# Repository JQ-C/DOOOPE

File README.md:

# DOOOPE. Real or Fake?

DOOOPE Keyboard is a 34-key wireless split keyboard. That uses Redragon low profile switches.

## Design Philosophy
DOOOPE was created with these in mind
- Budget at each category (MCU, Switch, Keycaps)
- Modular & Reusable parts
- Low Cost
- Low Profile
- Wireless
- 34 keys

# Resources

[Here](Kicad) you can find the Kicad files. 
<br>
[ZMK Config](https://github.com/JQ-C/zmk-config) for the DOOOPE using Xiao BLe

# Bill of Material
The link provided will be actual store i bought from but not affiliated with.
|Component|Amount|Remarks|Link|
|:----|:----|:----|:----|
|DOOOPE PCB|2|-| |
|SEEED Xiao BLE|2|-|[Cytron](https://my.cytron.io/p-seeed-xiao-ble-nrf52840-bluetooth-5p0)|
|Rechargeable Battery|2|28 x 18mm max| |
|Reset Switch|2|Through hole| |
|Power Switch|2|MSK12C02| [Shopee](https://shopee.com.my/10PCS-Slide-Switch-Micro-power-Toggle-Switch-Single-and-Double-row-Direct-inserted-Horizontal-Sliding-Second-Gear-Third-Gear-i.313127058.3661530160)|
|Pogo Pins|4|5mm|[Aliexpress](https://www.aliexpress.com/item/1005004016701633.html)|
|Redragon Switches|34|5mm|[Shopee](https://shopee.com.my/Redragon-SMD-RGB-MX-Low-Profile-Switch-3-Pin-for-Keyboard-Red-Black-Blue-Brown-i.326526863.10495732994?)|
|2mm male socket pins|4|1x7| |
|2.54 machine header pins|4|1x7| |
|JST PH 2.0 Connetor|2 Pair |-|[Shopee](https://shopee.com.my/10Sets-Lot-PH2.0-PH-2mm-Connector-Straight-needle-Seat-Plug-Terminals-2P-3P-4P-5P-6P-7P-8P-9P-10P-Connector-Pitch-2.0-i.313127058.5356644366?xptdk=3eb6c85b-3d97-453c-a1a4-ad3d53b7b325)|

# Build Guide
Coming soon <br>
The build guide for the DOOOPE keyboard can be found [here]()

# Project Reason
- DOOOPE keyboard was created to use Redragon low profile switch as a cheap alternative to the Low profile choc switches used in many Low-pro boards, hence the name "DOOOPE" that sounds like dupe.
- Another decision is to use off the shelf components and the cheapest at each category.
- This keyboard also used [Ergogen V4]() to prototype the layout and later finished in Kicad.

# Credits & Learning Resources

## Credits
1. Overall inspiration is the execellent keyboard [Totem by GEIST](https://github.com/GEIGEIGEIST/TOTEM)
2. The exposed copper art is inspired by [Urchin by Kyek](https://github.com/duckyb/urchin)
3. The special "negative silkscreen" and overall silkscreen style by [Dilemma by bastardkb](https://github.com/Bastardkb/Dilemma)
4. Pogo pin footprint from [Tlalocohyla Smithii by LuarRaNa](https://github.com/LuarRaNa/tlalocohyla_smithii)
5. Switch and much more footprint from [FingerPunch by SadekBaroudi](https://github.com/sadekbaroudi/fingerpunch)

I also want to thank the very helpful people in the [FingerPunch Discord]() that help guide me with the PCB creation.

## Learning Resources
The execellent [Ergogen Guide](https://web.archive.org/web/20230508055048/https://flatfootfox.com/ergogen-introduction/) by @FlatFootFox from the [Ergogen Discord](http://discord.ergogen.xyz/). Fall into the rabbit hole now with [Ergogen WebUI](https://ergogen.cache.works/). <br>

Great Non-keyboard Kicad Guide to get comfortable with the tool [STM32 PCB Design by Phils Lab](https://www.youtube.com/watch?v=aVUqaB0IMh4).

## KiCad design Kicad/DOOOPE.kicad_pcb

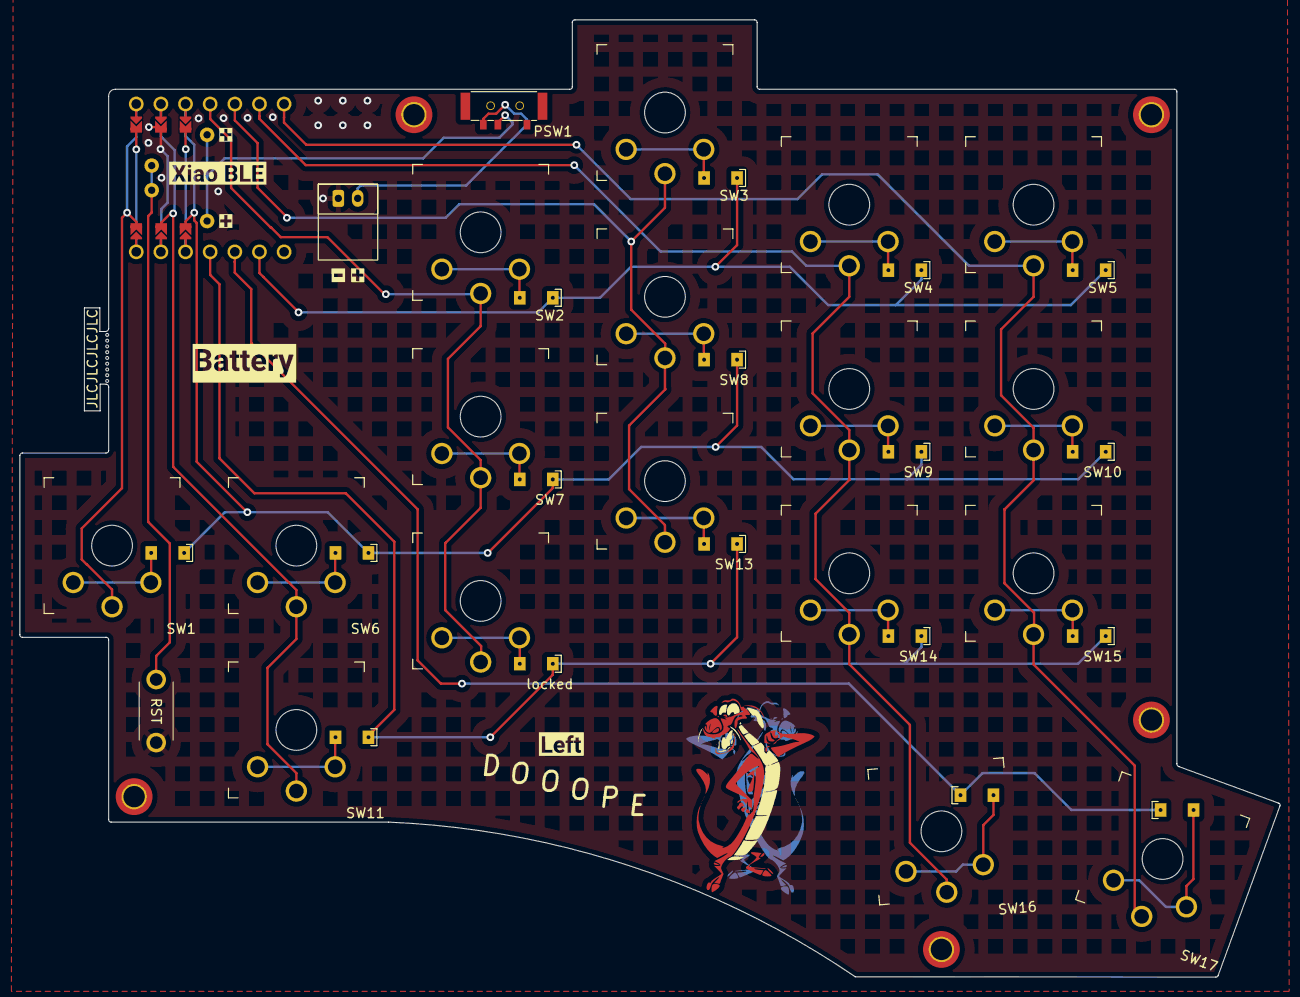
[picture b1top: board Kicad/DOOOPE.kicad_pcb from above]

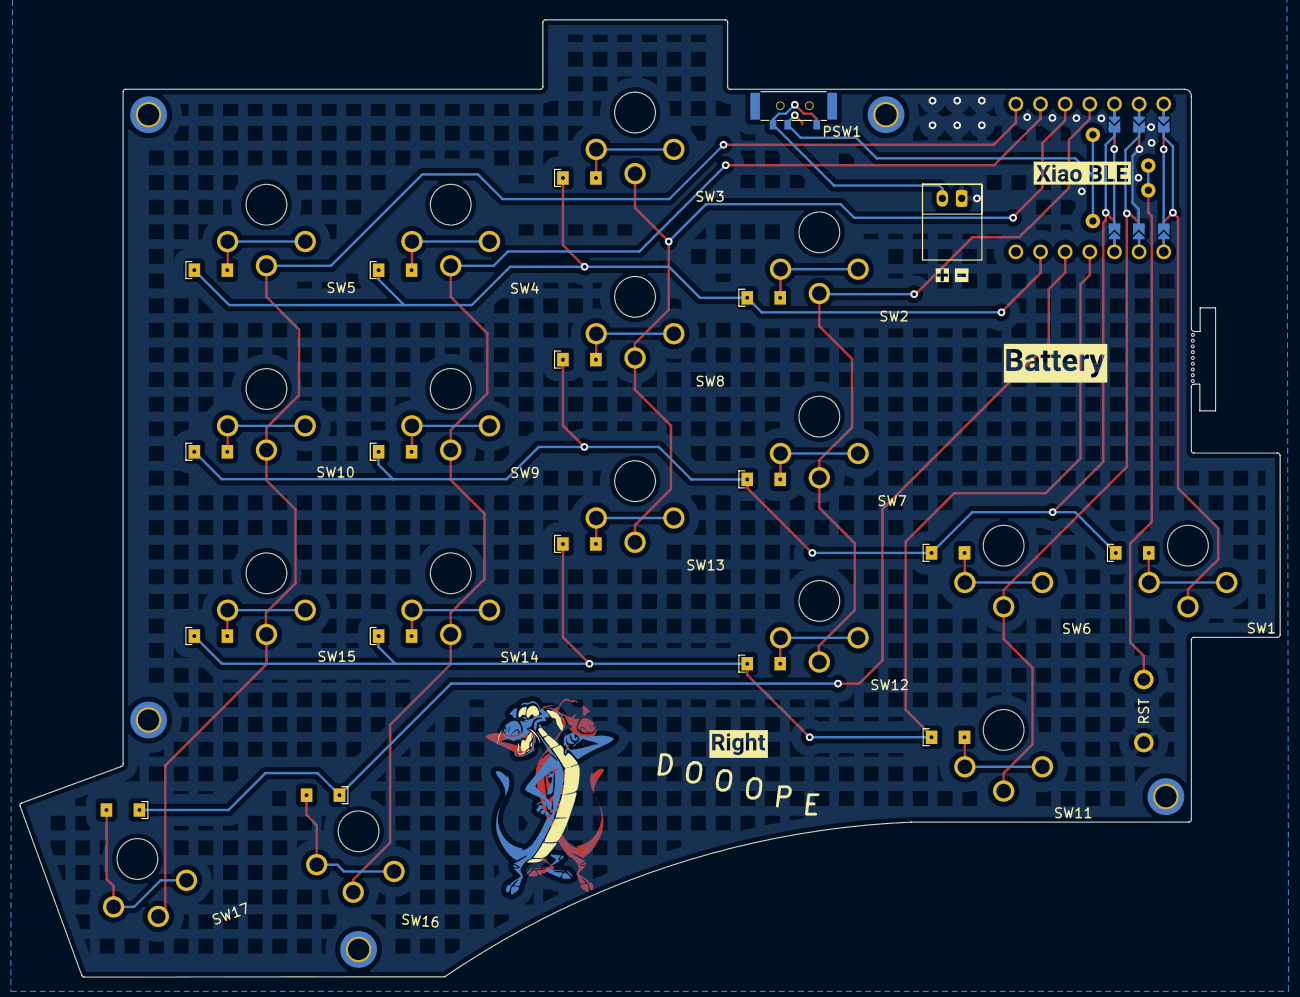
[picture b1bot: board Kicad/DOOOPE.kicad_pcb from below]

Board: 2 copper layers, 129.9 x 98.7 mm, 51 parts (6 on the bottom side), 31 nets.

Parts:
D1, D2, D3, D4, D5, D6, D7, D8, D9, D10, D11, D12, D13, D14, D15, D16, D17: 1N4148W; Diode SMD THT
J2: JST Connector; JST_PH_S2B-PH-K_1x02_P2.00mm_Horizontal
PSW1, PSW1#2: SW_SPDT; Power Switch
S1: 95C04A3T; Reset Switch
SW1, SW2, SW3, SW4, SW5, SW6, SW7, SW8, SW9, SW10, SW11, SW13, SW14, SW15, SW16, SW17: SW_PUSH; Redragon_LP_Reversible
U1: xiao-ble; Xiao BLE Rev Pogo
kibuzzard-643B780C: G***; kibuzzard-643B780C
kibuzzard-643B7631, kibuzzard-643B7631#2: G***; kibuzzard-643B7631
kibuzzard-643B7841: G***; kibuzzard-643B7841
kibuzzard-643B7985, kibuzzard-643B7985#2, kibuzzard-643B7985#3, kibuzzard-643B7985#4: G***; kibuzzard-643B7985
kibuzzard-6465F412, kibuzzard-6465F412#2: G***; kibuzzard-6465F412
kibuzzard-6465FBCD, kibuzzard-6465FBCD#2: G***; kibuzzard-6465FBCD
locked: SW_PUSH; Redragon_LP_Reversible

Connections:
BAT+: PSW1.2 (B), PSW1#2.2 (B), U1.19 (BAT)
Col0: SW1.1, U1.1 (A2/0.02_H)
Col1: SW6.1, SW11.1, U1.2 (A4/0.03_H)
Col2: SW2.1, SW7.1, U1.11 (A6_MOSI/1.15), locked.1
Col3: SW3.1, SW8.1, SW13.1, U1.10 (A5_MISO/1.14)
Col4: SW4.1, SW9.1, SW14.1, SW16.1, U1.9 (A7_SCK/1.13)
Col5: SW5.1, SW10.1, SW15.1, SW17.1, U1.8 (B9_RX/1.12)
GND: J2.1, S1.T2 (NO), U1.13 (GND)
unnamed: D1.2 (A), SW1.2
unnamed: D2.2 (A), SW2.2
unnamed: D3.2 (A), SW3.2
unnamed: D4.2 (A), SW4.2
unnamed: D5.2 (A), SW5.2
unnamed: D6.2 (A), SW6.2
unnamed: D7.2 (A), SW7.2
unnamed: D8.2 (A), SW8.2
unnamed: D9.2 (A), SW9.2
unnamed: D10.2 (A), SW10.2
unnamed: D11.2 (A), SW11.2
unnamed: D12.2 (A), locked.2
unnamed: D13.2 (A), SW13.2
unnamed: D14.2 (A), SW14.2
unnamed: D15.2 (A), SW15.2
unnamed: D16.2 (A), SW16.2
unnamed: D17.2 (A), SW17.2
RST: S1.T1 (COM), U1.17 (RESET)
Row0: D2.1 (K), D3.1 (K), D4.1 (K), D5.1 (K), U1.6 (A9_SCL/0.05_H)
Row1: D1.1 (K), D6.1 (K), D7.1 (K), D8.1 (K), D9.1 (K), D10.1 (K), U1.3 (A10/0.28)
Row2: D11.1 (K), D12.1 (K), D13.1 (K), D14.1 (K), D15.1 (K), U1.4 (A11/0.29)
Row3: D16.1 (K), D17.1 (K), U1.5 (A8_SDA/0.04_H)
VBAT: J2.2, PSW1.3 (C), PSW1#2.3 (C)

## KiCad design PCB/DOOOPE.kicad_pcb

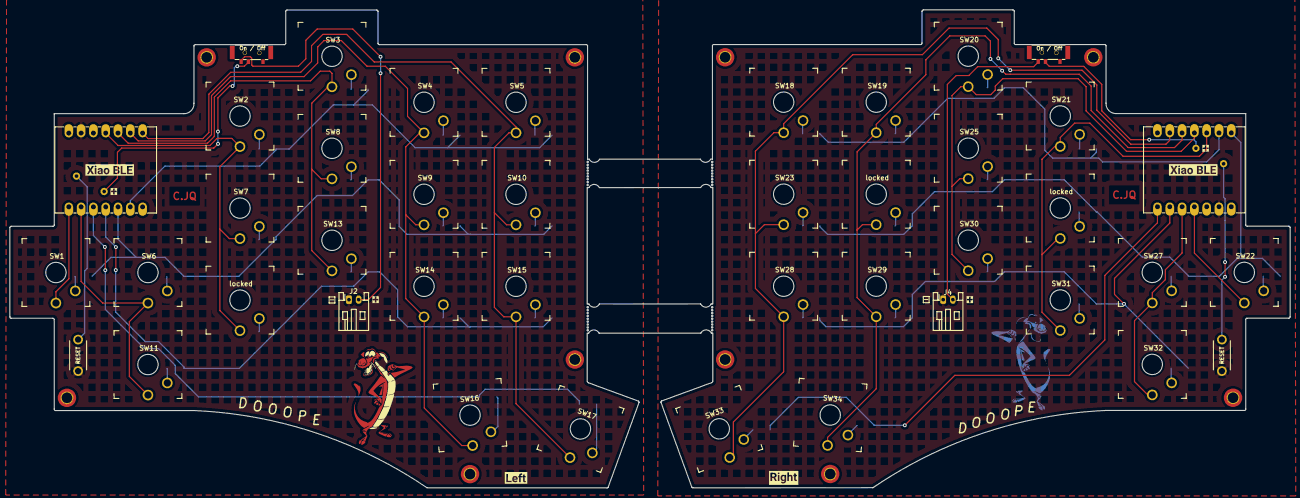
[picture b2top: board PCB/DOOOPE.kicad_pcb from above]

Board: 2 copper layers, 264.3 x 98.7 mm, 84 parts (0 on the bottom side), 62 nets.

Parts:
D1, D2, D3, D4, D5, D6, D7, D8, D9, D10, D11, D12, D13, D14, D15, D16, D17, D18, D19, D20, D21, D22, D23, D24, D25, D26, D27, D28, D29, D30, D31, D32, D33, D34: 1N4148W; SMD Diode
J2, J4: JST Connector; JST_PH_S2B-PH-K_1x02_P2.00mm_Horizontal
On / Off: SW_SPDT; Power Switch
On / Off#2: SW_SPDT; Power Switch
RESET: SW_Push; Reset Switch
RESET#2: SW_Push; Reset Switch
SW1, SW2, SW3, SW4, SW5, SW6, SW7, SW8, SW9, SW10, SW11, SW13, SW14, SW15, SW16, SW17, SW18, SW19, SW20, SW21, SW22, SW23, SW25, SW27, SW28, SW29, SW30, SW31, SW32, SW33, SW34: SW_PUSH; Redragon_LP
U1, U2: xiao-ble; xiao-ble-tht_copy
kibuzzard-643B780C: G***; kibuzzard-643B780C
kibuzzard-643B7631, kibuzzard-643B7631#2: G***; kibuzzard-643B7631
kibuzzard-643B7841: G***; kibuzzard-643B7841
kibuzzard-643B7985, kibuzzard-643B7985#2, kibuzzard-643B7985#3, kibuzzard-643B7985#4: G***; kibuzzard-643B7985
locked: SW_PUSH; Redragon_LP
locked#2, locked#3: SW_PUSH; Redragon_LP

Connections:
L_BAT+: On / Off.2 (B), U1.19 (BAT)
L_Col0: SW1.1, U1.1 (A2/0.02_H)
L_Col1: SW6.1, SW11.1, U1.2 (A4/0.03_H)
L_Col2: SW2.1, SW7.1, U1.11 (A6_MOSI/1.15), locked#2.1
L_Col3: SW3.1, SW8.1, SW13.1, U1.10 (A5_MISO/1.14)
L_Col4: SW4.1, SW9.1, SW14.1, SW16.1, U1.9 (A7_SCK/1.13)
L_Col5: SW5.1, SW10.1, SW15.1, SW17.1, U1.8 (B9_RX/1.12)
L_GND: J2.1, RESET#2.T2, U1.13 (GND)
L_RST: RESET#2.T1, U1.17 (RESET)
L_Row0: D2.1 (K), D3.1 (K), D4.1 (K), D5.1 (K), U1.6 (A9_SCL/0.05_H)
L_Row1: D1.1 (K), D6.1 (K), D7.1 (K), D8.1 (K), D9.1 (K), D10.1 (K), U1.5 (A8_SDA/0.04_H)
L_Row2: D11.1 (K), D12.1 (K), D13.1 (K), D14.1 (K), D15.1 (K), U1.4 (A11/0.29)
L_Row3: D16.1 (K), D17.1 (K), U1.3 (A10/0.28)
L_VBAT: J2.2, On / Off.3 (C)
unnamed: D1.2 (A), SW1.2
unnamed: D2.2 (A), SW2.2
unnamed: D3.2 (A), SW3.2
unnamed: D4.2 (A), SW4.2
unnamed: D5.2 (A), SW5.2
unnamed: D6.2 (A), SW6.2
unnamed: D7.2 (A), SW7.2
unnamed: D8.2 (A), SW8.2
unnamed: D9.2 (A), SW9.2
unnamed: D10.2 (A), SW10.2
unnamed: D11.2 (A), SW11.2
unnamed: D12.2 (A), locked#2.2
unnamed: D13.2 (A), SW13.2
unnamed: D14.2 (A), SW14.2
unnamed: D15.2 (A), SW15.2
unnamed: D16.2 (A), SW16.2
unnamed: D17.2 (A), SW17.2
unnamed: D18.2 (A), SW18.2
unnamed: D19.2 (A), SW19.2
unnamed: D20.2 (A), SW20.2
unnamed: D21.2 (A), SW21.2
unnamed: D22.2 (A), SW22.2
unnamed: D23.2 (A), SW23.2
unnamed: D24.2 (A), locked.2
unnamed: D25.2 (A), SW25.2
unnamed: D26.2 (A), locked#3.2
unnamed: D27.2 (A), SW27.2
unnamed: D28.2 (A), SW28.2
unnamed: D29.2 (A), SW29.2
unnamed: D30.2 (A), SW30.2
unnamed: D31.2 (A), SW31.2
unnamed: D32.2 (A), SW32.2
unnamed: D33.2 (A), SW33.2
unnamed: D34.2 (A), SW34.2
R_BAT+: On / Off#2.2 (B), U2.19 (BAT)
R_Col0: SW18.1, SW23.1, SW28.1, SW33.1, U2.6 (A9_SCL/0.05_H)
R_Col1: SW19.1, SW29.1, SW34.1, U2.5 (A8_SDA/0.04_H), locked.1
R_Col2: SW20.1, SW25.1, SW30.1, U2.4 (A11/0.29)
R_Col3: SW21.1, SW31.1, U2.3 (A10/0.28), locked#3.1
R_Col4: SW27.1, SW32.1, U2.10 (A5_MISO/1.14)
R_Col5: SW22.1, U2.11 (A6_MOSI/1.15)
R_GND: J4.1, RESET.T1, U2.13 (GND)
R_RST: RESET.T2, U2.17 (RESET)
R_Row0: D18.1 (K), D19.1 (K), D20.1 (K), D21.1 (K), U2.2 (A4/0.03_H)
R_Row1: D22.1 (K), D23.1 (K), D24.1 (K), D25.1 (K), D26.1 (K), D27.1 (K), U2.1 (A2/0.02_H)
R_Row2: D28.1 (K), D29.1 (K), D30.1 (K), D31.1 (K), D32.1 (K), U2.9 (A7_SCK/1.13)
R_Row3: D33.1 (K), D34.1 (K), U2.8 (B9_RX/1.12)
R_VBAT: J4.2, On / Off#2.3 (C)

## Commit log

2023-04-18 Create images
2023-04-18 Added images
2023-04-23 Add info to readme
2023-04-23 added future rev + todo
2023-05-08 Restructure project into Rev 1 & 2
2023-05-08 Added R2 kicad files
2023-05-08 fix link
2023-05-08 link fix
2023-05-08 add more info to readme
2023-05-11 Restructure repo
2023-05-11 Update read me
2023-07-20 latest files
